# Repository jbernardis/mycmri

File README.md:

# mycmri
## DIY CMRI ecosystem for model railroad automation

This is very much a work in progress.  At this point, the following eagle designs are mature:

- blockocchexdelay - a single board with 6 DCC block occupancy detectors that immediately detect block entry, but do not report block exit until approximately 1 second after train actually leaves block.

- 2 byte input - a circuit design based on 74hc165 shift registers to pull in data from inputs such as buttons, block occupancy detectors, etc.

- 1 byte input - a 1 shift register version of the above.

- 2 byte output with darlington open collector with a darlington array in the output stream to support other devices such as motors and relays - circuit sink.

All other designs are very early in their life and have not been tested/debugged:

- node - an arduino based circuit that can shift in data from many inputs, shift out data to many outputs, drive servos through an adafruit PWM servo driver board, and report all of this back to a host PC (running JMRI?) via an RS485 bus.    This circuit may also provide 5 volt power to this ecosystem.

- 1 byte output version of the above

- relay boards designed to work with the output boards, 2 and 4 relay variants

- others as needs/inspirations arise.  Support for DCC Reverser and CD discharge unit is also being considered.

Arduino code will be provided as node functionality is implemented

Linux-based driver code is also part of this repository and is in very early development.

Slowly moving PCB design to kicad.  Both kicad and eagle designs will be included here, at least until the first boards are fabricated and tested from the kicad designs.

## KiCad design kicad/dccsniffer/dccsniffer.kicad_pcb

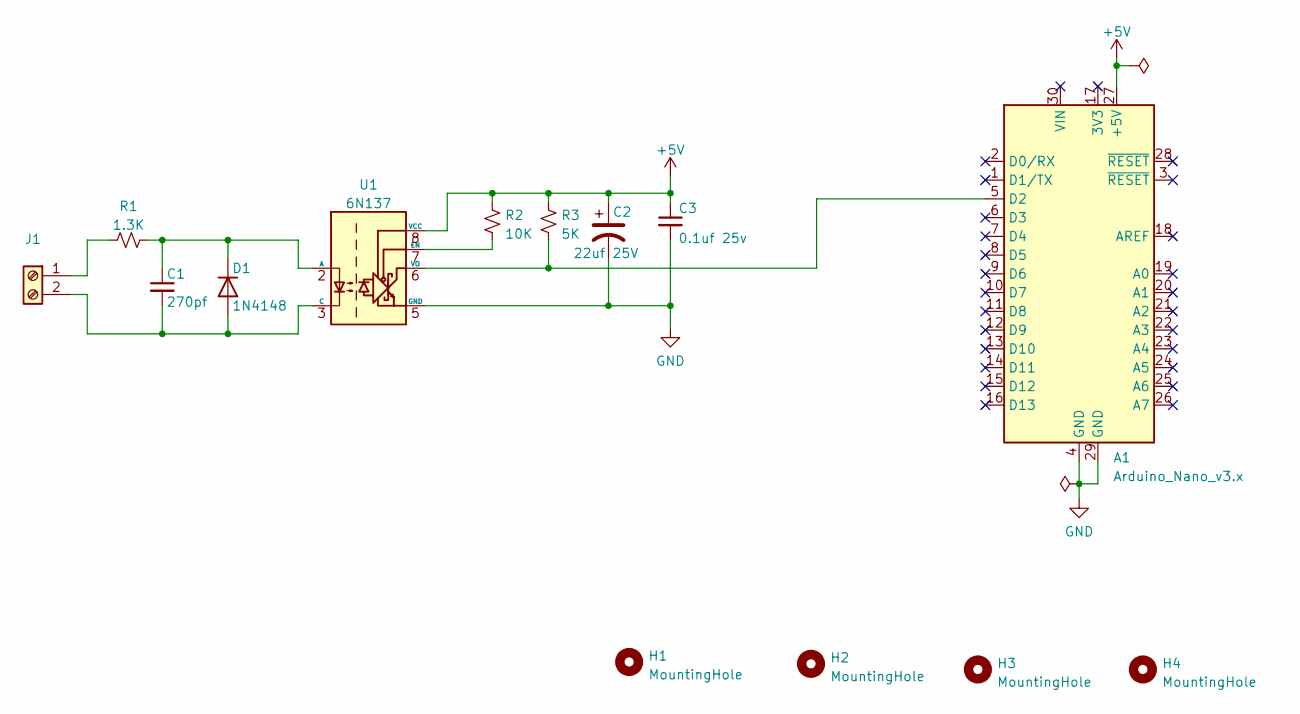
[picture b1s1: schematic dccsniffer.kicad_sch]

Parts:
A1: Arduino_Nano_v3.x; Arduino_Nano
C1: 270pf; C_Disc_D5.0mm_W2.5mm_P5.00mm
C2: 22uf 25V; CP_Radial_D5.0mm_P2.50mm
C3: 0.1uf 25v; C_Disc_D5.0mm_W2.5mm_P5.00mm
D1: 1N4148; D_DO-35_SOD27_P7.62mm_Horizontal
H1, H2, H3, H4: MountingHole; MountingHole_3.2mm_M3
J1: TerminalBlock_Phoenix_MKDS-1,5-2-5.08_1x02_P5.08mm_Horizont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
R1: 1.3K; R_Axial_DIN0309_L9.0mm_D3.2mm_P12.70mm_Horizontal
R2: 10K; R_Axial_DIN0309_L9.0mm_D3.2mm_P12.70mm_Horizontal
R3: 5K; R_Axial_DIN0309_L9.0mm_D3.2mm_P12.70mm_Horizontal
U1: 6N137; DIP-8_W7.62mm

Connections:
+5V: A1.27 (+5V), C2.1, C3.1, R2.1, R3.1, U1.8 (VCC)
GND: A1.4 (GND), A1.29 (GND), C2.2, C3.2, U1.5 (GND)
unnamed: A1.5 (D2), R3.2, U1.6 (VO)
unnamed: C1.1, D1.1 (K), R1.2, U1.2 (A)
unnamed: C1.2, D1.2 (A), J1.2, U1.3 (C)
unnamed: J1.1, R1.1
unnamed: R2.2, U1.7 (EN)

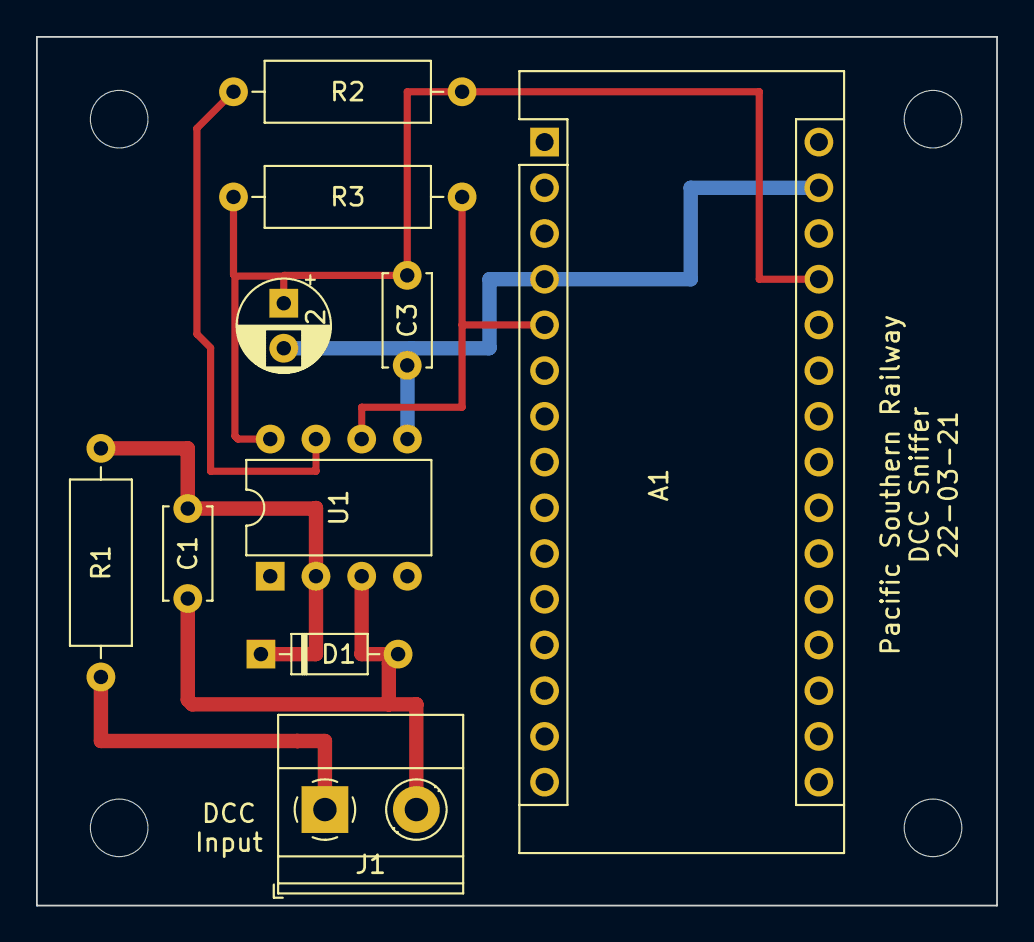
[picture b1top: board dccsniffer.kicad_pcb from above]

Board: 2 copper layers, 53.3 x 48.3 mm, 14 parts (0 on the bottom side), 7 nets.

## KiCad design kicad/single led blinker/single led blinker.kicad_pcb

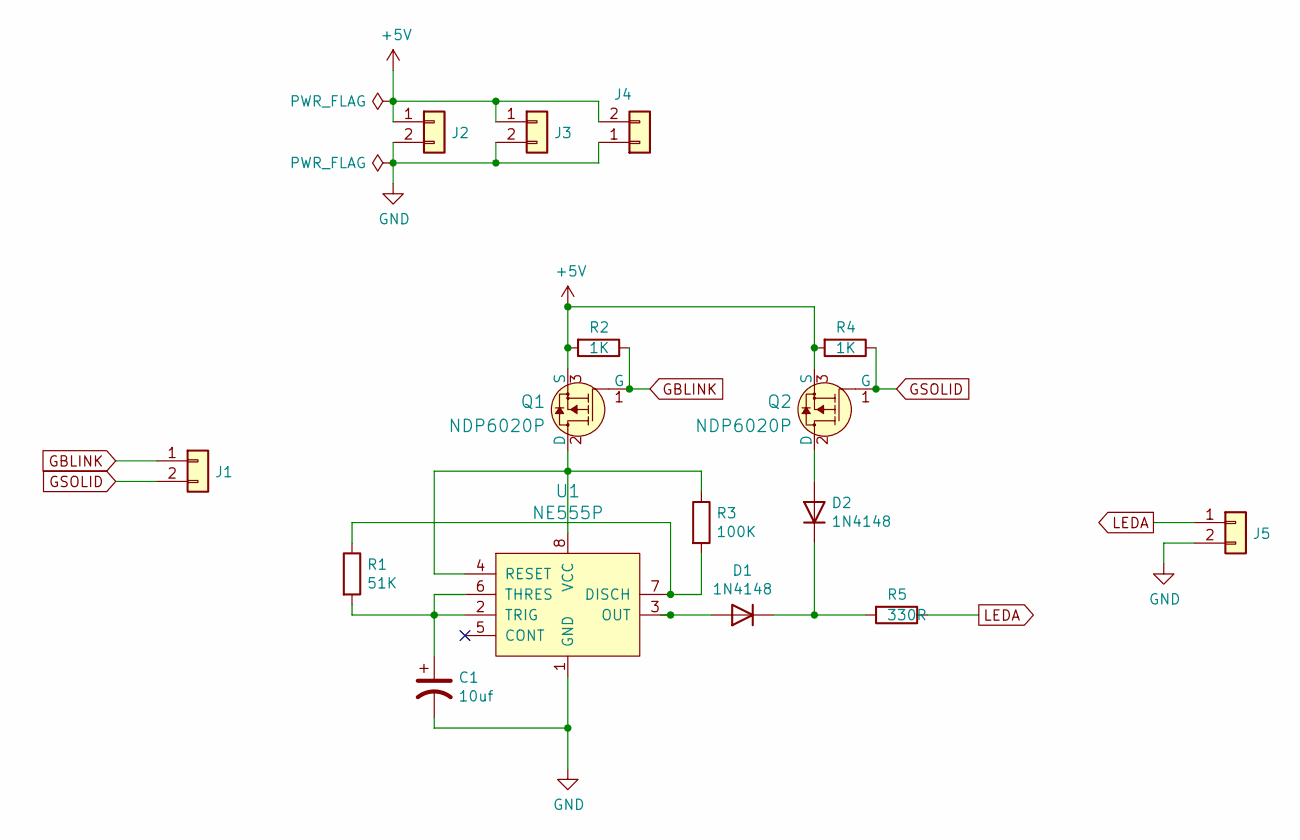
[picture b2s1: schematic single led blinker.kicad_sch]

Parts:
C1: 10uf; CP_Radial_D8.0mm_P3.50mm
D1, D2: 1N4148; D_DO-35_SOD27_P7.62mm_Horizontal
J1, J4, J5: Conn_01x02; TerminalBlock_Phoenix_MKDS-1,5-2-5.08_1x02_P5.08mm_Horizont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
J2: Conn_01x02; PinHeader_1x02_P2.54mm_Horizontal
J3: Conn_01x02; PinSocket_1x02_P2.54mm_Horizontal
Q1, Q2: NDP6020P; TO-220-3_Vertical; MPN NDP60020P; Digi-Key_PN NDP6020P-ND
R1: 51K; R_Axial_DIN0207_L6.3mm_D2.5mm_P10.16mm_Horizontal
R2, R4: 1K; R_Axial_DIN0207_L6.3mm_D2.5mm_P10.16mm_Horizontal
R3: 100K; R_Axial_DIN0207_L6.3mm_D2.5mm_P10.16mm_Horizontal
R5: 330R; R_Axial_DIN0207_L6.3mm_D2.5mm_P10.16mm_Horizontal
U1: NE555P; DIP-8_W7.62mm; MPN NE555P; Digi-Key_PN 296-1411-5-ND

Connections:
+5V: J2.1, J3.1, J4.2, Q1.3 (S), Q2.3 (S), R2.2, R4.2
GBLINK: J1.1, Q1.1 (G), R2.1
GND: C1.2, J2.2, J3.2, J4.1, J5.2, U1.1 (GND)
GSOLID: J1.2, Q2.1 (G), R4.1
LEDA: J5.1, R5.1
unnamed: C1.1, R1.2, U1.2 (TRIG), U1.6 (THRES)
unnamed: D1.1 (K), D2.1 (K), R5.2
unnamed: D1.2 (A), U1.3 (OUT)
unnamed: D2.2 (A), Q2.2 (D)
unnamed: Q1.2 (D), R3.1, U1.4 (RESET), U1.8 (VCC)
unnamed: R1.1, R3.2, U1.7 (DISCH)

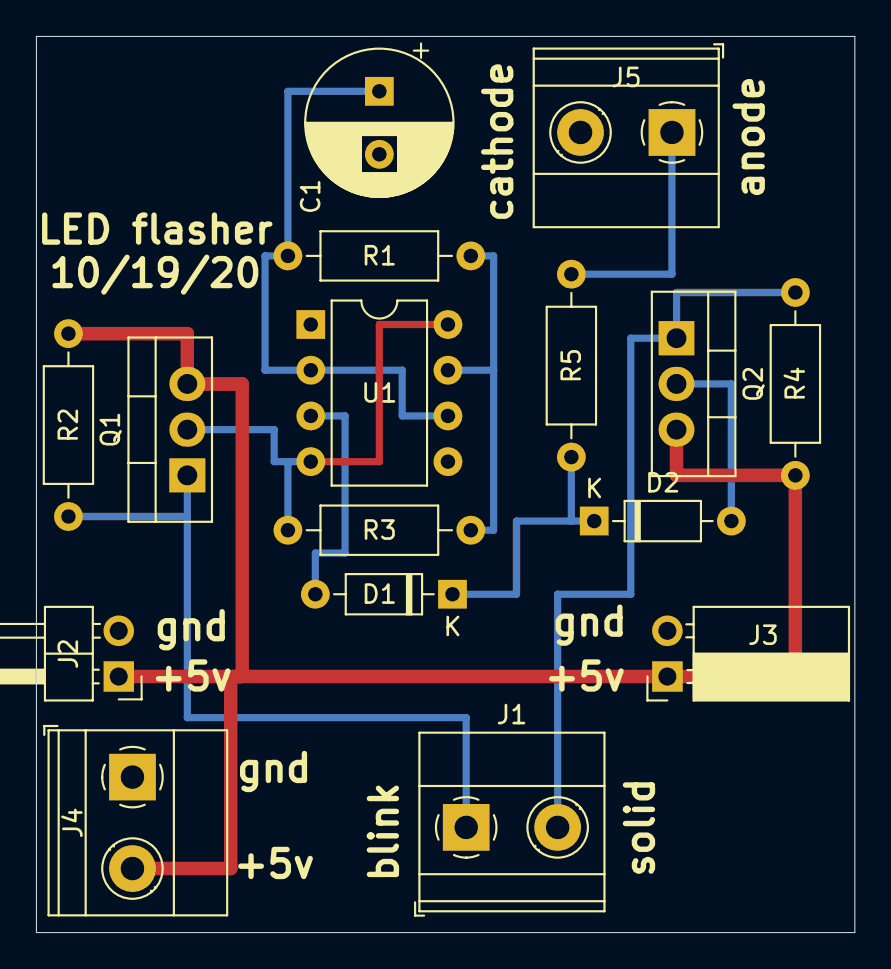
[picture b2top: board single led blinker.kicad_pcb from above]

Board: 2 copper layers, 45.5 x 49.8 mm, 16 parts (0 on the bottom side), 11 nets.

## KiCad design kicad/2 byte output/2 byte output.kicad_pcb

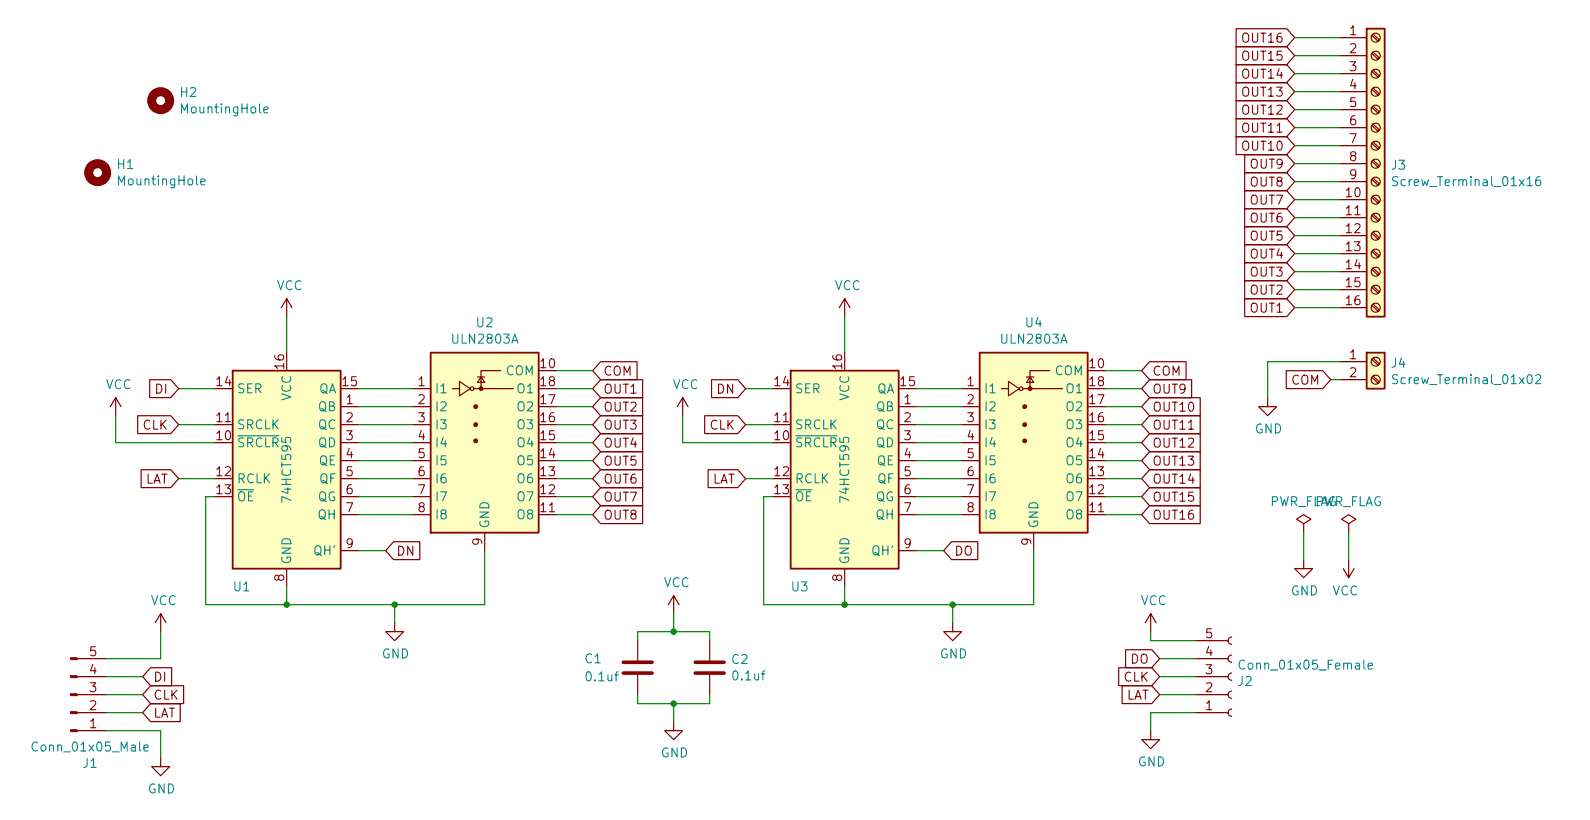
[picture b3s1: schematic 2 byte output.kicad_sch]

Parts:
C1, C2: 0.1uf; C_Disc_D3.4mm_W2.1mm_P2.50mm
H1, H2: MountingHole; MountingHole_3.2mm_M3
J1: Conn_01x05_Male; PinHeader_1x05_P2.54mm_Horizontal
J2: Conn_01x05_Female; PinSocket_1x05_P2.54mm_Horizontal
J3: Screw_Terminal_01x16; TerminalBlock_Phoenix_MKDS-1,5-16-5.08_1x16_P5.08mm_Horizon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
J4: Screw_Terminal_01x02; TerminalBlock_Phoenix_MKDS-1,5-2-5.08_1x02_P5.08mm_Horizont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
U1, U3: 74HCT595; DIP-16_W7.62mm
U2, U4: ULN2803A; DIP-18_W7.62mm

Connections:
CLK: J1.3, J2.3, U1.11 (SRCLK), U3.11 (SRCLK)
COM: J4.2, U2.10 (COM), U4.10 (COM)
DI: J1.4, U1.14 (SER)
DN: U1.9 (QH'), U3.14 (SER)
DO: J2.4, U3.9 (QH')
GND: C1.2, C2.2, J1.1, J2.1, J4.1, U1.8 (GND), U1.13 (~OE), U2.9 (GND), U3.8 (GND), U3.13 (~OE), U4.9 (GND)
LAT: J1.2, J2.2, U1.12 (RCLK), U3.12 (RCLK)
unnamed: U1.1 (QB), U2.2 (I2)
unnamed: U1.2 (QC), U2.3 (I3)
unnamed: U1.3 (QD), U2.4 (I4)
unnamed: U1.4 (QE), U2.5 (I5)
unnamed: U1.5 (QF), U2.6 (I6)
unnamed: U1.6 (QG), U2.7 (I7)
unnamed: U1.7 (QH), U2.8 (I8)
unnamed: U1.15 (QA), U2.1 (I1)
unnamed: U3.1 (QB), U4.2 (I2)
unnamed: U3.2 (QC), U4.3 (I3)
unnamed: U3.3 (QD), U4.4 (I4)
unnamed: U3.4 (QE), U4.5 (I5)
unnamed: U3.5 (QF), U4.6 (I6)
unnamed: U3.6 (QG), U4.7 (I7)
unnamed: U3.7 (QH), U4.8 (I8)
unnamed: U3.15 (QA), U4.1 (I1)
OUT1: J3.16, U2.18 (O1)
OUT2: J3.15, U2.17 (O2)
OUT3: J3.14, U2.16 (O3)
OUT4: J3.13, U2.15 (O4)
OUT5: J3.12, U2.14 (O5)
OUT6: J3.11, U2.13 (O6)
OUT7: J3.10, U2.12 (O7)
OUT8: J3.9, U2.11 (O8)
OUT9: J3.8, U4.18 (O1)
OUT10: J3.7, U4.17 (O2)
OUT11: J3.6, U4.16 (O3)
OUT12: J3.5, U4.15 (O4)
OUT13: J3.4, U4.14 (O5)
OUT14: J3.3, U4.13 (O6)
OUT15: J3.2, U4.12 (O7)
OUT16: J3.1, U4.11 (O8)
VCC: C1.1, C2.1, J1.5, J2.5, U1.10 (~SRCLR), U1.16 (VCC), U3.10 (~SRCLR), U3.16 (VCC)

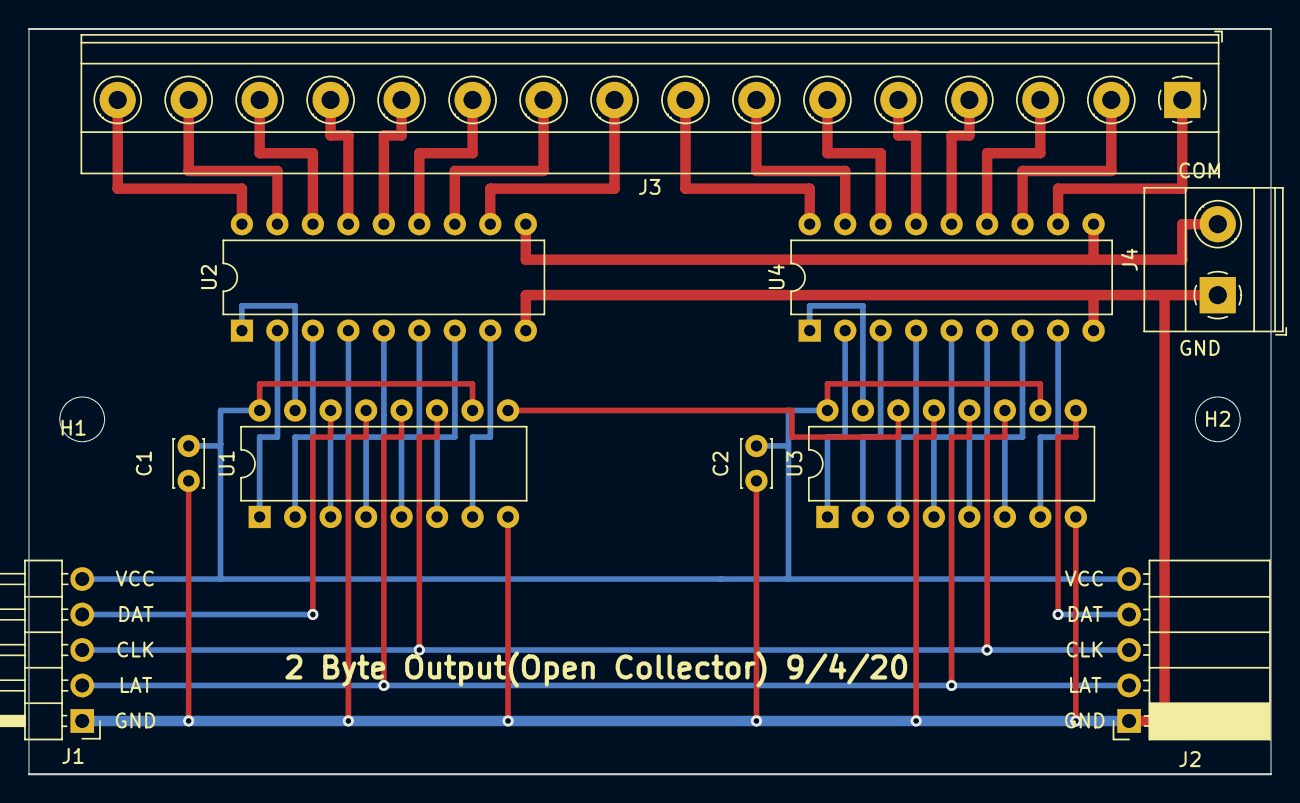
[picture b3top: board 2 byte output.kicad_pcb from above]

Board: 2 copper layers, 88.9 x 53.3 mm, 12 parts (0 on the bottom side), 40 nets.

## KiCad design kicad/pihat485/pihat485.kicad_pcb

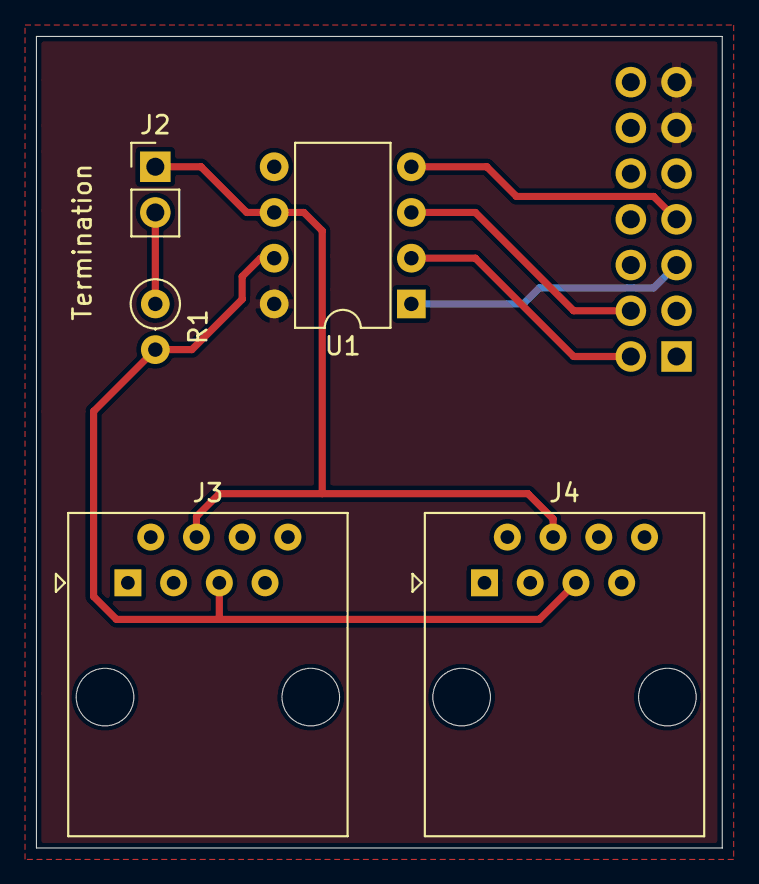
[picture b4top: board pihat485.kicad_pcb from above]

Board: 2 copper layers, 38.1 x 45.1 mm, 6 parts (1 on the bottom side), 9 nets.

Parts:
J1: Conn_02x07_Odd_Even; PinSocket_2x07_P2.54mm_Vertical
J2: Conn_01x02; PinHeader_1x02_P2.54mm_Vertical
J3, J4: RJ45; RJ45_Amphenol_54602-x08_Horizontal
R1: 120R; R_Axial_DIN0207_L6.3mm_D2.5mm_P2.54mm_Vertical
U1: MAX485E; DIP-8_W7.62mm

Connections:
A: J2.1, J3.4, J4.4, U1.6
B: J3.5, J4.5, R1.2, U1.7
DE: J1.4, U1.3
DI: J1.7, U1.4
GND: J1.1, J1.6, J1.9, J3.1, J3.2, J4.1, J4.2, U1.5
unnamed: J2.2, R1.1
RE: J1.2, U1.2
RO: J1.5, U1.1
VCC: J1.11, J1.13, U1.8

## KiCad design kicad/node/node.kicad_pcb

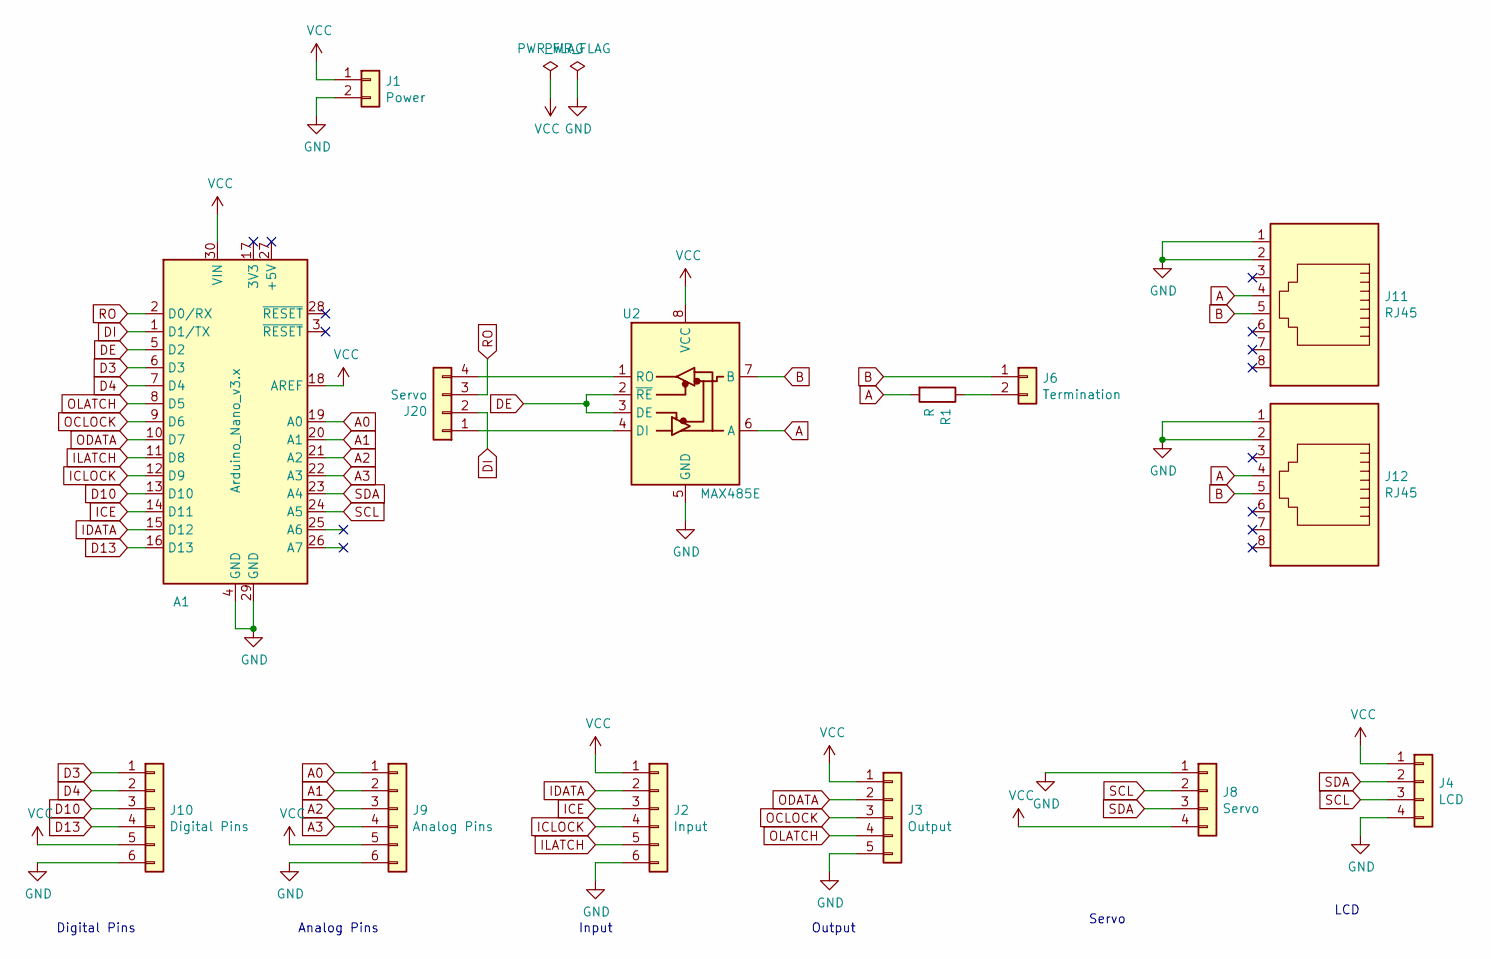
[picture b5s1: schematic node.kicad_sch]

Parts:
A1: Arduino_Nano_v3.x; Arduino_Nano
J1: Power; TerminalBlock_Phoenix_MKDS-1,5-2-5.08_1x02_P5.08mm_Horizont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
J2: Input; PinHeader_1x06_P2.54mm_Horizontal
J3: Output; PinHeader_1x05_P2.54mm_Horizontal
J4: LCD; PinHeader_1x04_P2.54mm_Horizontal
J6: Termination; PinHeader_1x02_P2.54mm_Vertical
J8: Servo; PinHeader_1x04_P2.54mm_Horizontal
J9: Analog Pins; PinHeader_1x06_P2.54mm_Vertical
J10: Digital Pins; PinHeader_1x06_P2.54mm_Vertical
J11, J12: RJ45; RJ45_Amphenol_54602-x08_Horizontal
J20: Servo; PinHeader_1x04_P2.54mm_Vertical
R1: R; R_Axial_DIN0207_L6.3mm_D2.5mm_P2.54mm_Vertical
U2: MAX485E; DIP-8_W7.62mm

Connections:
A: J11.4, J12.4, R1.2, U2.6 (A)
A0: A1.19 (A0), J9.1
A1: A1.20 (A1), J9.2
A2: A1.21 (A2), J9.3
A3: A1.22 (A3), J9.4
B: J6.1, J11.5, J12.5, U2.7 (B)
D3: A1.6 (D3), J10.1
D4: A1.7 (D4), J10.2
D10: A1.13 (D10), J10.3
D13: A1.16 (D13), J10.4
DE: A1.5 (D2), U2.2 (~RE), U2.3 (DE)
DI: A1.1 (D1/TX), J20.2
GND: A1.4 (GND), A1.29 (GND), J1.2, J2.6, J3.5, J4.4, J8.1, J9.6, J10.6, J11.1, J11.2, J12.1, J12.2, U2.5 (GND)
ICE: A1.14 (D11), J2.3
ICLOCK: A1.12 (D9), J2.4
IDATA: A1.15 (D12), J2.2
ILATCH: A1.11 (D8), J2.5
unnamed: J6.2, R1.1
unnamed: J20.1, U2.4 (DI)
unnamed: J20.4, U2.1 (RO)
OCLOCK: A1.9 (D6), J3.3
ODATA: A1.10 (D7), J3.2
OLATCH: A1.8 (D5), J3.4
RO: A1.2 (D0/RX), J20.3
SCL: A1.24 (A5), J4.3, J8.2
SDA: A1.23 (A4), J4.2, J8.3
VCC: A1.18 (AREF), A1.30 (VIN), J1.1, J2.1, J3.1, J4.1, J8.4, J9.5, J10.5, U2.8 (VCC)

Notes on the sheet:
Digital Pins
Output
Servo
Analog Pins
Input
LCD

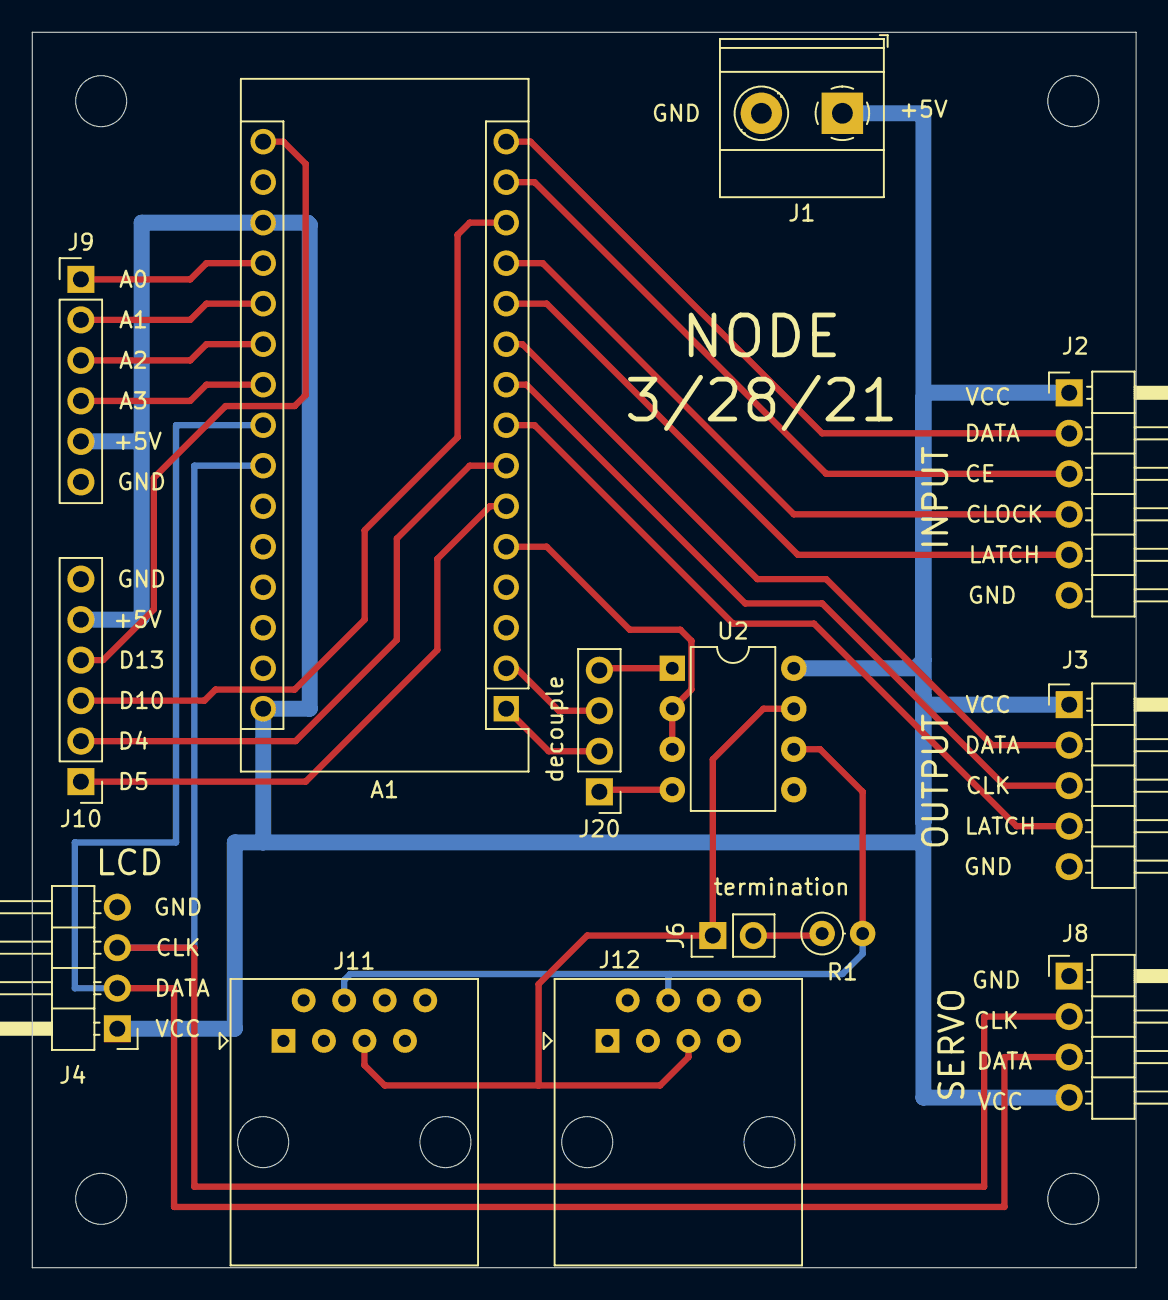
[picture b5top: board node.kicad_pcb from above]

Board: 2 copper layers, 69.2 x 77.5 mm, 18 parts (0 on the bottom side), 27 nets.

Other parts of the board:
 : MountingHole_3.2mm_M3
 #2,  #3,  #4: MountingHole_3.2mm_M3

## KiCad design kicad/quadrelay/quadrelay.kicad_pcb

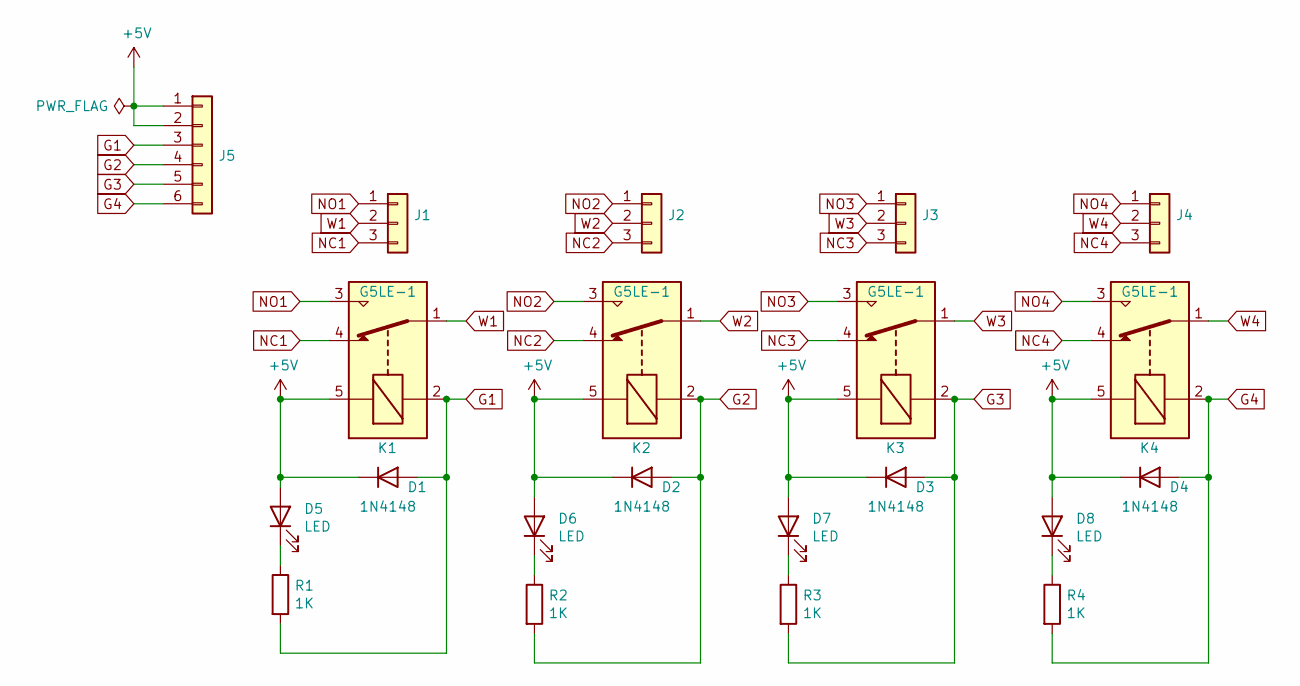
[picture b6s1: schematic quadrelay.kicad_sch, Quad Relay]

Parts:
D1, D2, D3, D4: 1N4148; D_DO-35_SOD27_P7.62mm_Horizontal
D5, D6, D7, D8: LED; LED_D3.0mm
J1, J2, J3, J4: Conn_01x03; TerminalBlock_Phoenix_MKDS-1,5-3-5.08_1x03_P5.08mm_Horizont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
J5: Conn_01x06; TerminalBlock_Phoenix_MKDS-1,5-6-5.08_1x06_P5.08mm_Horizont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
K1, K2, K3, K4: G5LE-1; Relay_SPDT_Omron-G5LE-1
R1, R2, R3, R4: 1K; R_Axial_DIN0309_L9.0mm_D3.2mm_P5.08mm_Vertical

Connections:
+5V: D1.1 (K), D2.1 (K), D3.1 (K), D4.1 (K), D5.2 (A), D6.2 (A), D7.2 (A), D8.2 (A), J5.1, J5.2, K1.5, K2.5, K3.5, K4.5
G1: D1.2 (A), J5.3, K1.2, R1.2
G2: D2.2 (A), J5.4, K2.2, R2.2
G3: D3.2 (A), J5.5, K3.2, R3.2
G4: D4.2 (A), J5.6, K4.2, R4.2
NC1: J1.3, K1.4
NC2: J2.3, K2.4
NC3: J3.3, K3.4
NC4: J4.3, K4.4
NO1: J1.1, K1.3
NO2: J2.1, K2.3
NO3: J3.1, K3.3
NO4: J4.1, K4.3
unnamed: D5.1 (K), R1.1
unnamed: D6.1 (K), R2.1
unnamed: D7.1 (K), R3.1
unnamed: D8.1 (K), R4.1
W1: J1.2, K1.1
W2: J2.2, K2.1
W3: J3.2, K3.1
W4: J4.2, K4.1

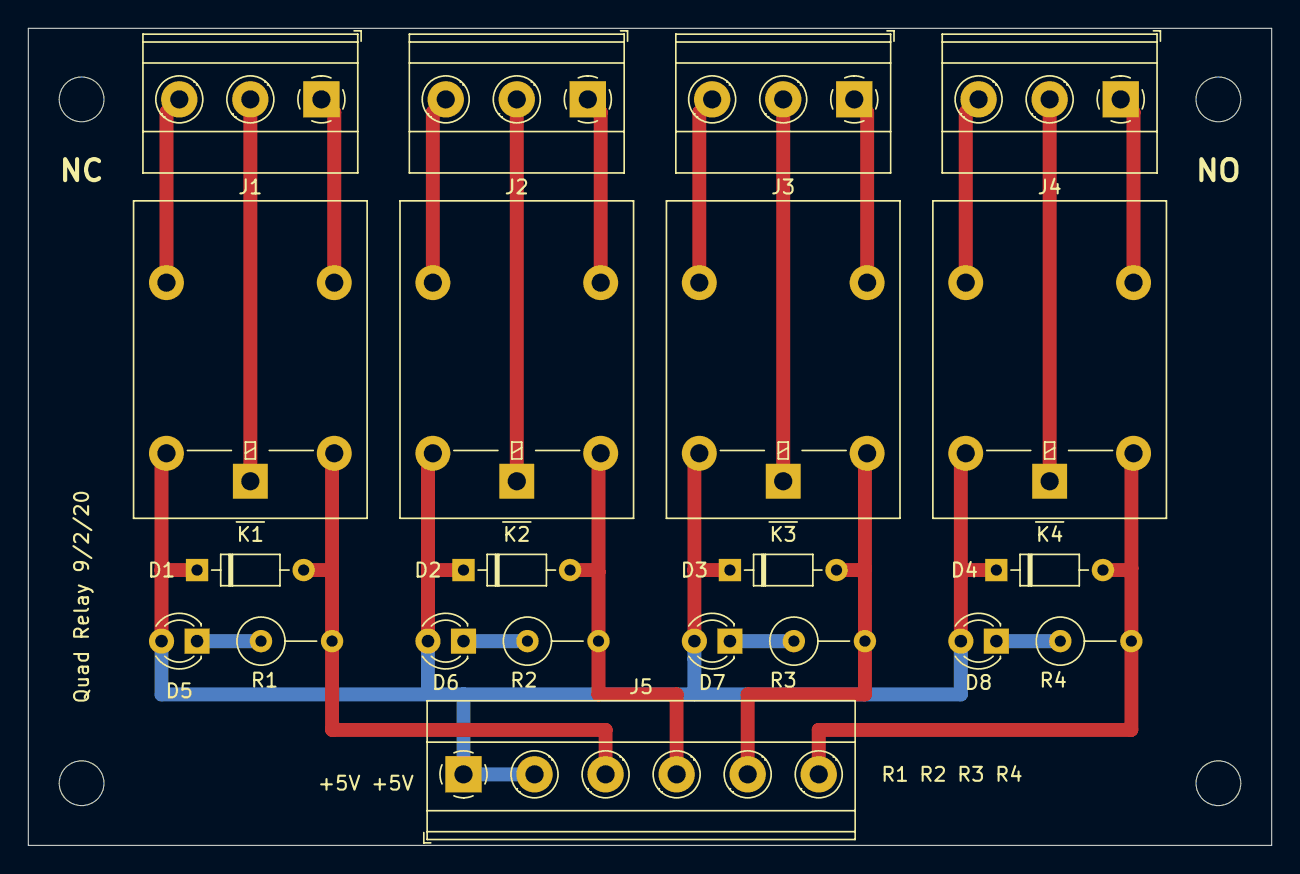
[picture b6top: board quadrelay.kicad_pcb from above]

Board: 2 copper layers, 88.9 x 58.4 mm, 25 parts (0 on the bottom side), 21 nets.

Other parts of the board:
 : MountingHole_3.2mm_M3
 #2,  #3,  #4: MountingHole_3.2mm_M3

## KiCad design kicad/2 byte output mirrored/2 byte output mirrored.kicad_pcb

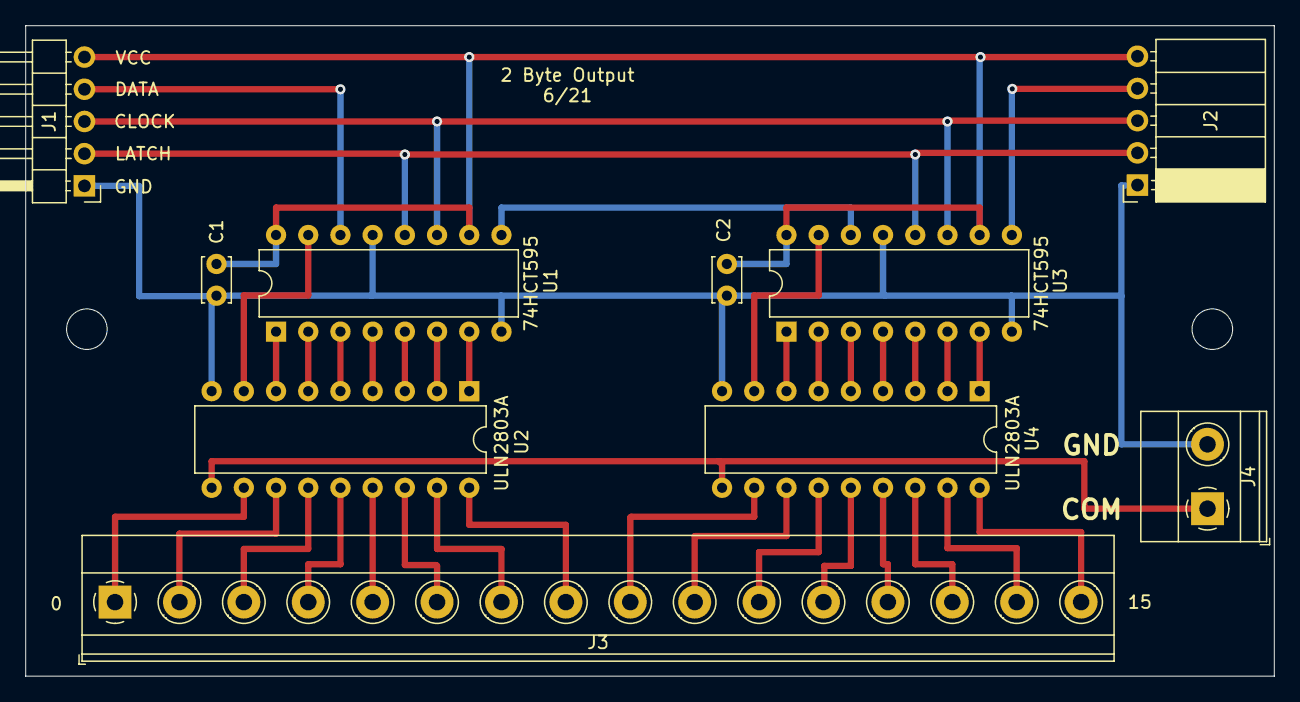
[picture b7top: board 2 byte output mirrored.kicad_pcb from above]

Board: 2 copper layers, 98.5 x 51.3 mm, 12 parts (0 on the bottom side), 40 nets.

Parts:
 : MountingHole_3.2mm_M3
 #2: MountingHole_3.2mm_M3
C1, C2: 0.1uf; C_Disc_D3.4mm_W2.1mm_P2.50mm
J1: Conn_01x05_Male; PinHeader_1x05_P2.54mm_Horizontal
J2: Conn_01x05_Female; PinSocket_1x05_P2.54mm_Horizontal
J3: Screw_Terminal_01x16; TerminalBlock_Phoenix_MKDS-1,5-16-5.08_1x16_P5.08mm_Horizon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
J4: Screw_Terminal_01x02; TerminalBlock_Phoenix_MKDS-1,5-2-5.08_1x02_P5.08mm_Horizont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
U1, U3: 74HCT595; DIP-16_W7.62mm
U2, U4: ULN2803A; DIP-18_W7.62mm

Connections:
CLK: J1.3, J2.3, U1.11, U3.11
COM: J4.1, U2.10, U4.10
DI: J1.4, U1.14
DN: U1.9, U3.14
DO: J2.4, U3.9
GND: C1.2, C2.2, J1.1, J2.1, J4.2, U1.8, U1.13, U2.9, U3.8, U3.13, U4.9
I1: U1.7, U2.1
I2: U1.6, U2.2
I3: U1.5, U2.3
I4: U1.4, U2.4
I5: U1.3, U2.5
I6: U1.2, U2.6
I7: U1.1, U2.7
I8: U1.15, U2.8
I9: U3.7, U4.1
I10: U3.6, U4.2
I11: U3.5, U4.3
I12: U3.4, U4.4
I13: U3.3, U4.5
I14: U3.2, U4.6
I15: U3.1, U4.7
I16: U3.15, U4.8
LAT: J1.2, J2.2, U1.12, U3.12
OUT1: J3.1, U2.11
OUT2: J3.2, U2.12
OUT3: J3.3, U2.13
OUT4: J3.4, U2.14
OUT5: J3.5, U2.15
OUT6: J3.6, U2.16
OUT7: J3.7, U2.17
OUT8: J3.8, U2.18
OUT9: J3.9, U4.11
OUT10: J3.10, U4.12
OUT11: J3.11, U4.13
OUT12: J3.12, U4.14
OUT13: J3.13, U4.15
OUT14: J3.14, U4.16
OUT15: J3.15, U4.17
OUT16: J3.16, U4.18
VCC: C1.1, C2.1, J1.5, J2.5, U1.10, U1.16, U3.10, U3.16

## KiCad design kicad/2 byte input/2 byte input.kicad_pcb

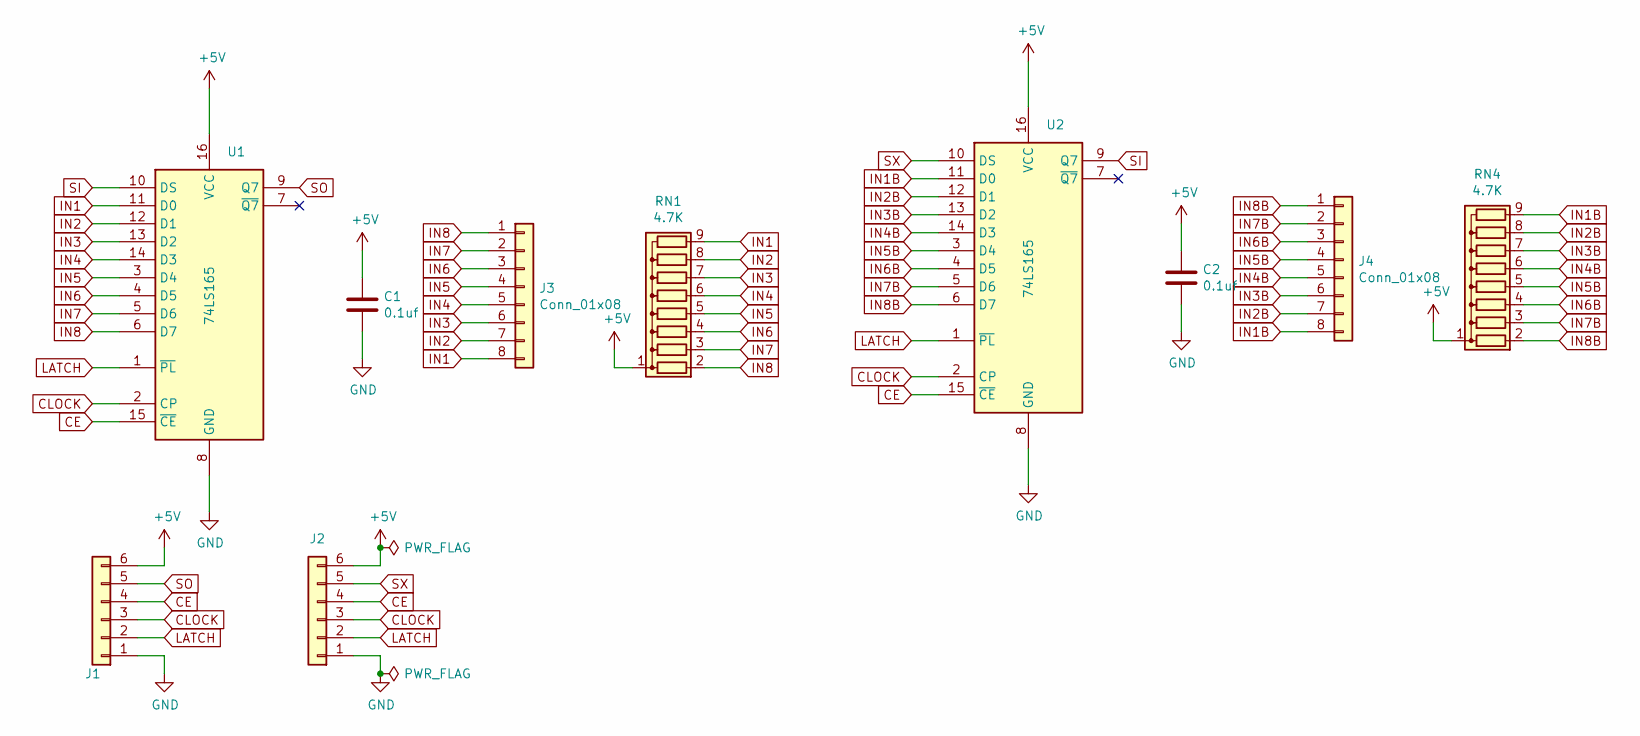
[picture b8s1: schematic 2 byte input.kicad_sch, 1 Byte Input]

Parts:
C1, C2: 0.1uf; C_Disc_D5.0mm_W2.5mm_P2.50mm
J1: Conn_01x06; PinHeader_1x06_P2.54mm_Horizontal
J2: Conn_01x06; PinSocket_1x06_P2.54mm_Horizontal
J3, J4: Conn_01x08; TerminalBlock_Phoenix_MKDS-1,5-8-5.08_1x08_P5.08mm_Horizont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
RN1, RN4: 4.7K; R_Array_SIP9
U1, U2: 74LS165; DIP-16_W7.62mm

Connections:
+5V: C1.1, C2.1, J1.6, J2.6, RN1.1 (common), RN4.1 (common), U1.16 (VCC), U2.16 (VCC)
CE: J1.4, J2.4, U1.15 (~CE), U2.15 (~CE)
CLOCK: J1.3, J2.3, U1.2 (CP), U2.2 (CP)
GND: C1.2, C2.2, J1.1, J2.1, U1.8 (GND), U2.8 (GND)
IN1: J3.8, RN1.9 (R8), U1.11 (D0)
IN1B: J4.8, RN4.9 (R8), U2.11 (D0)
IN2: J3.7, RN1.8 (R7), U1.12 (D1)
IN2B: J4.7, RN4.8 (R7), U2.12 (D1)
IN3: J3.6, RN1.7 (R6), U1.13 (D2)
IN3B: J4.6, RN4.7 (R6), U2.13 (D2)
IN4: J3.5, RN1.6 (R5), U1.14 (D3)
IN4B: J4.5, RN4.6 (R5), U2.14 (D3)
IN5: J3.4, RN1.5 (R4), U1.3 (D4)
IN5B: J4.4, RN4.5 (R4), U2.3 (D4)
IN6: J3.3, RN1.4 (R3), U1.4 (D5)
IN6B: J4.3, RN4.4 (R3), U2.4 (D5)
IN7: J3.2, RN1.3 (R2), U1.5 (D6)
IN7B: J4.2, RN4.3 (R2), U2.5 (D6)
IN8: J3.1, RN1.2 (R1), U1.6 (D7)
IN8B: J4.1, RN4.2 (R1), U2.6 (D7)
LATCH: J1.2, J2.2, U1.1 (~PL), U2.1 (~PL)
SI: U1.10 (DS), U2.9 (Q7)
SO: J1.5, U1.9 (Q7)
SX: J2.5, U2.10 (DS)

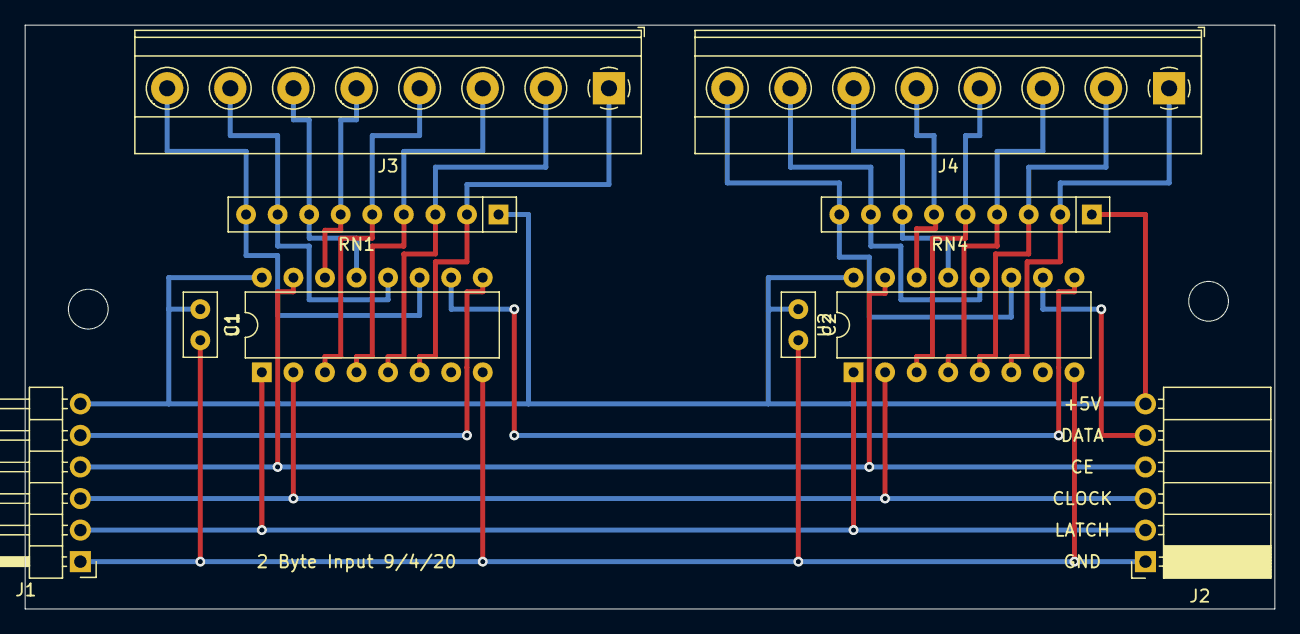
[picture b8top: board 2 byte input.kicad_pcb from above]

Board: 2 copper layers, 100.6 x 47.0 mm, 10 parts (0 on the bottom side), 24 nets.

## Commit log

2019-07-11 initial commit of current eagle designs
2019-08-20 check in changes
2019-08-20 updated readme to reflect last commit
2019-08-24 corrected circuit for input board
2019-08-30 periodic check in - everything working so far with breadboards.
2019-09-19 periodic check-in
2019-10-11 periodic check in
2019-10-11 added pdf file of schematics and boards, removed button debounce and servo driver
2020-08-04 periodic checkin
2020-09-06 adding kicad designs - deleting unwanted eagle designd
2020-09-07 check in
2020-09-07 renaming inputboard to be all lowercase
2020-09-08 added probe information to arduino sketch
2020-09-09 periodic checkin - adding a node config tool
2020-09-11 removed timing statements
2020-09-11 added pihat, minor fix to rrmain
2020-09-13 changed representation of outputs from 0/1 to False/True
2020-09-14 changed input report to use true/false instead of 0/1
2020-09-14 adding nodetester utility
2020-09-16 added code for new dialog boxes - missing fromlast commit
2020-09-17 added final few reports/commands
2020-09-17 added logic to reverse bit order in inputs report
2020-09-18 restructured projects to be compatible with eclipse
2020-09-18 more compatibility changes
2020-09-18 Added tool tips. added shutdown button
2020-09-18 moved trigger tables and surrounding logic to separate project
2020-09-18 beefed up nodecfg to take command line arguments
2020-09-18 fixed protocol error - also fixed a type
2020-09-19 added a menu, restructured logic selecting node
2020-09-20 Added simple framing logic to socket protocol
2020-09-20 beefed up socket protocol - minor fix in nodetester.py
2020-09-20 removed a debugging statement
2020-09-21 added logging
2020-09-21 Beefed up error handling
2020-09-21 Added node active/inactive status to towers report
2020-09-21 fixed small bug
2020-09-21 renamed towers report to nodes report
2020-09-21 added logging to http interface
2020-09-23 reorganizing directories - added trigger host application
2020-09-23 still restructuring
2020-09-23 completing logic for trigger app
2020-09-23 clean up
2020-09-26 removed "jmri" from names
2020-10-18 changed node selection to not allow selection of an inactive node
2020-10-18 fixed logic when choosing a node
2020-10-28 added logic for new command: toggle turnout
2020-10-30 fixes
2020-11-10 added circuit for led flasher, added toggle command
2020-11-10 added logic to search up one directory for config file
2020-11-14 adding flags and registers constructs - still need to add to trigger
2020-11-17 implemented flags and registers in trigger
2021-03-24 reimplementation of rules - use pseudo python instead of json
2021-03-25 documented the http interface and the rules file format
2021-03-25 Added outputs as a matching criteria for triggers
2021-03-28 All triggers MUST have an input as a decision criteria
2021-04-29 periodic checkin - also adding c++ code for reimplementation of server
2021-05-11 added error checking and recovert
2021-05-11 rerouted several PCBs
2021-05-15 added logging using BOOST logging
2021-05-22 trigger re-write to work with new c server
2021-05-22 syncing systems
2021-05-27 fixed format or nodesrpt, updated http documentation
2021-06-05 debugging
2021-06-09 updating for running on raspberry pi
2021-07-27 added new command - pulse - to send a timed pulse to putputs
2021-07-28 added 2 byte mirrored output
2021-07-28 changes to tester to handle pulsed output
2021-07-28 testing revealed bugs - fixes
2021-07-28 Fixed display message routine to show buffer instead of msg
2021-07-29 added pulse length to outputs dialog - still needs position adjustment
2021-07-30 formated the outputs dialog details
2021-08-01 Fixed representation of pulse, corrected servo report syntax
2021-08-02 adding recovery from down/failed nodes
2021-08-02 logic to restart failed nodes - paced out node starts/restarts
2021-08-02 more changes for recovery logic
2021-08-04 added bus timeout to config file
2021-08-05 changes to error handling
2021-08-05 still working on error handling
2021-08-05 aligned columns in noderpr log entry
2021-08-06 added labels to inputs dlg, worked on dlg positioning
2022-03-22 added dcc sniffer, conversion to kicad 6
2022-03-22 reorganized dccsniffer as a python project
2022-03-22 added gitignore for dccsniffer
2022-05-01 updated dcc sniffer pcs, new arduino sketch for dcc server
2023-01-10 added switchdriver sketch
2024-11-11 long overdue update
